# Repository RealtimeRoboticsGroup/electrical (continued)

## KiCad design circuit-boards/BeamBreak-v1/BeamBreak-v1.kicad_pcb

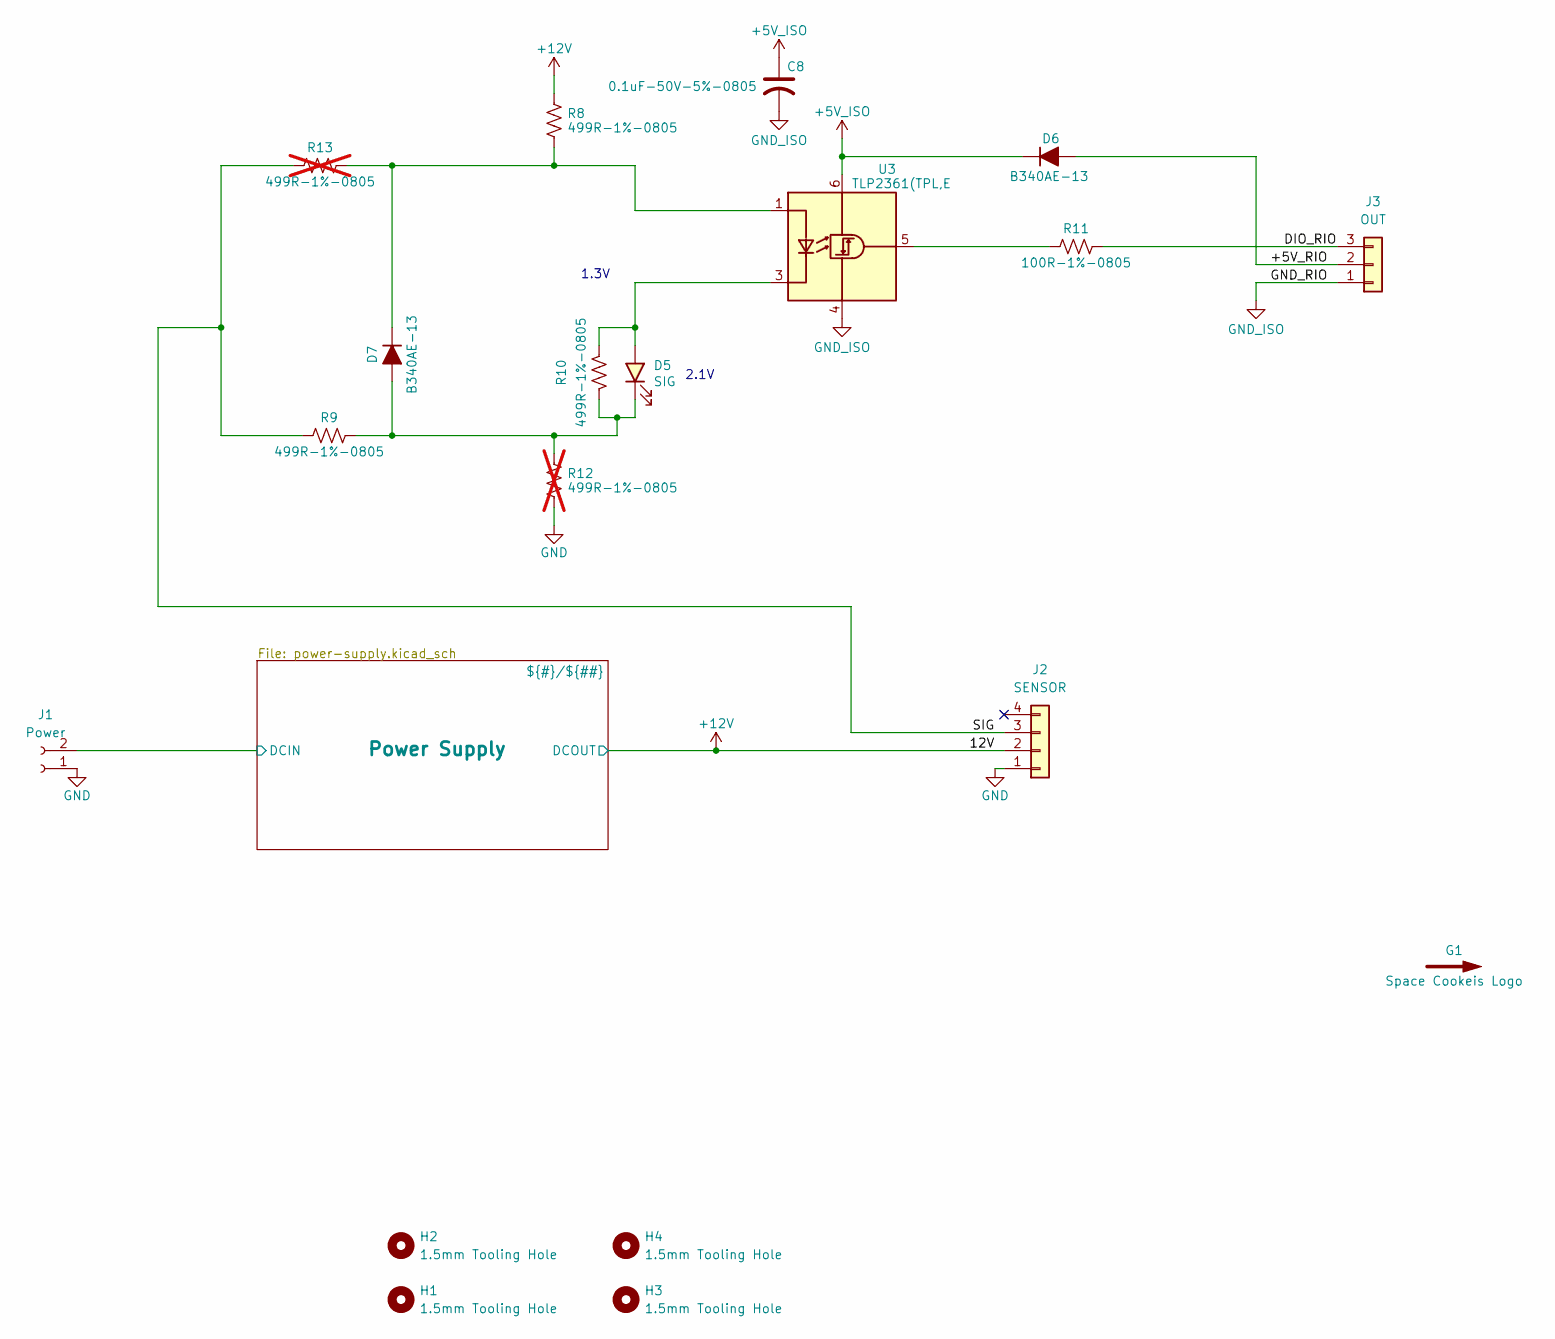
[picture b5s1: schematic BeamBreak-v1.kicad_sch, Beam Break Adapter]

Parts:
C8: 0.1uF-50V-5%-0805; C_0805_2012Metric_Pad1.18x1.45mm_HandSolder; MFG P/N C0805C104J5RACTU
D5: SIG; LED_1206_3216Metric; MFG P/N QTLP650D3TR
D6, D7: B340AE-13; D_SMA; MFG P/N B340AE-13
G1: Space Cookeis Logo; SPACE_COOKIES_LOGO_7mm
H1, H2, H3, H4: 1.5mm Tooling Hole; ToolingHole_1.5mm
J1: Power; Weidmuller-1824740000; MFG P/N 1824740000
J2: SENSOR; Molex-70555-0003; MFG P/N 70555-0038
J3: OUT; Molex-70555-0002; MFG P/N 70555-0037
R8, R9, R10: 499R-1%-0805; R_0805_2012Metric_Pad1.20x1.40mm_HandSolder; MFG P/N RC0805FR-07499RL
R11: 100R-1%-0805; R_0805_2012Metric_Pad1.20x1.40mm_HandSolder; MFG P/N CRG0805F100R
R12, R13: 499R-1%-0805; R_0805_2012Metric_Pad1.20x1.40mm_HandSolder; MFG P/N RC0805FR-07499RL; not fitted
U3: TLP2361(TPL,E; SO-5-6_4.55x3.7mm_P1.27mm; MFG P/N TLP2361(TPL,E

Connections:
+5V_ISO: C8.1, D6.1 (K), U3.6 (VDD)
+12V: J2.2, R8.2; also elsewhere on the board
/+5V_RIO: D6.2 (A), J3.2
/DIO_RIO: J3.3, R11.2
/Power Supply/DCIN: J1.2; also elsewhere on the board
/SIG: J2.3, R9.1, R13.1
GND: J1.1, J2.1, R12.1; also elsewhere on the board
GND_ISO: C8.2, J3.1, U3.4 (GND)
unnamed: D5.2 (A), R10.2, U3.3 (K)
unnamed: D5.1 (K), D7.2 (A), R9.2, R10.1, R12.2
unnamed: D7.1 (K), R8.1, R13.2, U3.1 (A)
unnamed: R11.1, U3.5 (VO)

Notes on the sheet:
2.1V
1.3V

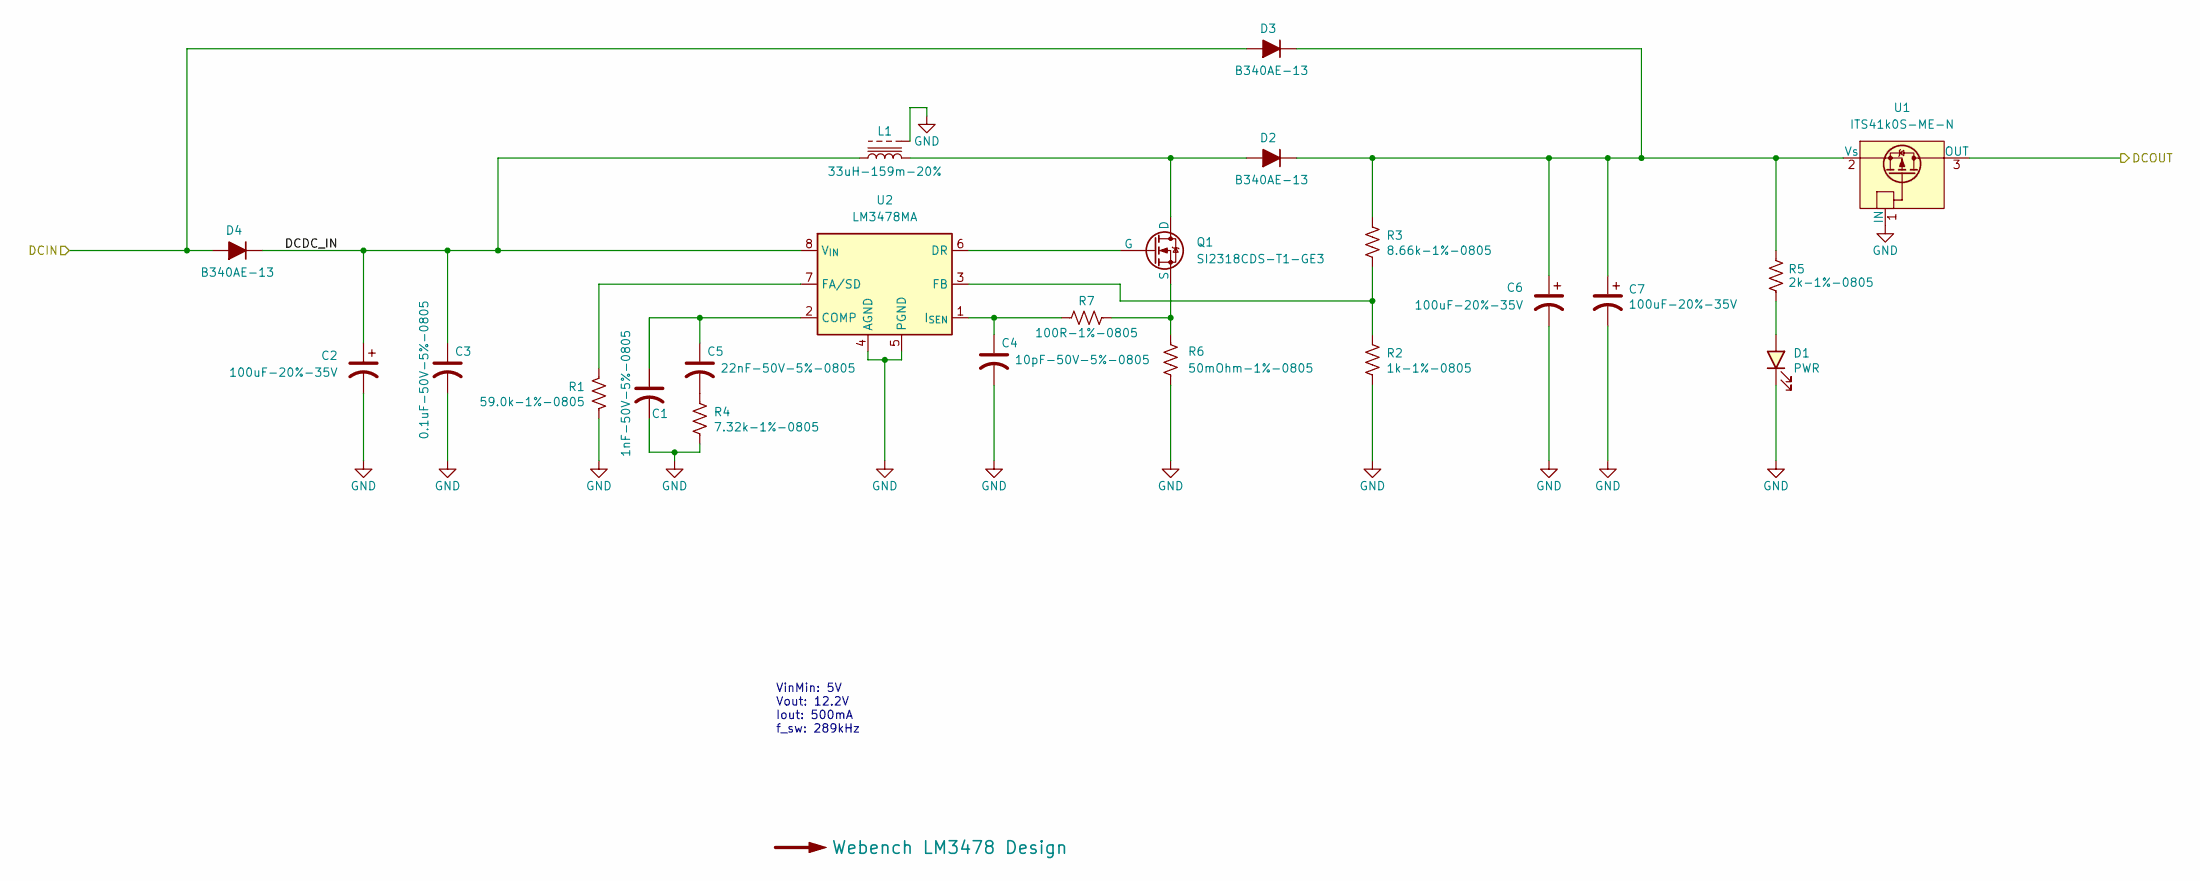
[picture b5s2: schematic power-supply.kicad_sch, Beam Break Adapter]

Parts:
C1: 1nF-50V-5%-0805; C_0805_2012Metric_Pad1.18x1.45mm_HandSolder; MFG P/N C0805C102J5GACTU
C2, C6, C7: 100uF-20%-35V; CP_Radial_D6.3mm_P2.50mm; MFG P/N RPF0608101M035K
C3: 0.1uF-50V-5%-0805; C_0805_2012Metric_Pad1.18x1.45mm_HandSolder; MFG P/N C0805C104J5RACTU
C4: 10pF-50V-5%-0805; C_0805_2012Metric_Pad1.18x1.45mm_HandSolder; MFG P/N CC0805JRNPO9BN100
C5: 22nF-50V-5%-0805; C_0805_2012Metric_Pad1.18x1.45mm_HandSolder; MFG P/N C2012C0G1H223J125AA
D1: PWR; LED_1206_3216Metric; MFG P/N QTLP650D4TR/QT15-21SYGD/S530-E2/TR8
D2, D3, D4: B340AE-13; D_SMA; MFG P/N B340AE-13
L1: 33uH-159m-20%; VishayDale-IHLE3232; MFG P/N IHLE3232DDER330M5A
Q1: SI2318CDS-T1-GE3; SOT-23-3; MFG P/N SI2318CDS-T1-GE3
R1: 59.0k-1%-0805; R_0805_2012Metric_Pad1.20x1.40mm_HandSolder; MFG P/N RC0805FR-0759KL
R2: 1k-1%-0805; R_0805_2012Metric_Pad1.20x1.40mm_HandSolder; MFG P/N RC0805FR-071KL
R3: 8.66k-1%-0805; R_0805_2012Metric_Pad1.20x1.40mm_HandSolder; MFG P/N RMCF0805FT8K66
R4: 7.32k-1%-0805; R_0805_2012Metric_Pad1.20x1.40mm_HandSolder; MFG P/N ERJ-6ENF7321V
R5: 2k-1%-0805; R_0805_2012Metric_Pad1.20x1.40mm_HandSolder; MFG P/N CRCW08052K00FKEA
R6: 50mOhm-1%-0805; R_0805_2012Metric_Pad1.20x1.40mm_HandSolder; MFG P/N ERJ-6BWFR050V
R7: 100R-1%-0805; R_0805_2012Metric_Pad1.20x1.40mm_HandSolder; MFG P/N CRG0805F100R
U1: ITS41k0S-ME-N; SOT-223-3_TabPin2; MFG P/N ITS41K0SMENHUMA1
U2: LM3478MA; SOIC-8_3.9x4.9mm_P1.27mm; MFG P/N LM3478MAX/NOPB

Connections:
+12V: U1.3 (OUT); also elsewhere on the board
/Power Supply/DCDC_IN: C2.1, C3.1, D4.1 (K), L1.1, U2.8 (V_{IN})
/Power Supply/DCIN: D3.2 (A), D4.2 (A); also elsewhere on the board
GND: C1.2, C2.2, C3.2, C4.2, C6.2, C7.2, D1.1 (K), L1.3, R1.1, R2.1, R4.1, R6.2, U1.1 (IN), U2.4 (AGND), U2.5 (PGND); also elsewhere on the board
unnamed: C5.2, R4.2
unnamed: D1.2 (A), R5.1
unnamed: D2.2 (A), L1.2, Q1.3 (D)
unnamed: C6.1, C7.1, D2.1 (K), D3.1 (K), R3.2, R5.2, U1.2 (Vs)
unnamed: Q1.1 (G), U2.6 (DR)
unnamed: Q1.2 (S), R6.1, R7.2
unnamed: C1.1, C5.1, U2.2 (COMP)
unnamed: R1.2, U2.7 (FA/SD)
unnamed: R2.2, R3.1, U2.3 (FB)
unnamed: C4.1, R7.1, U2.1 (I_{SEN})

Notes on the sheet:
VinMin: 5V Vout: 12.2V Iout: 500mA f_sw: 289kHz

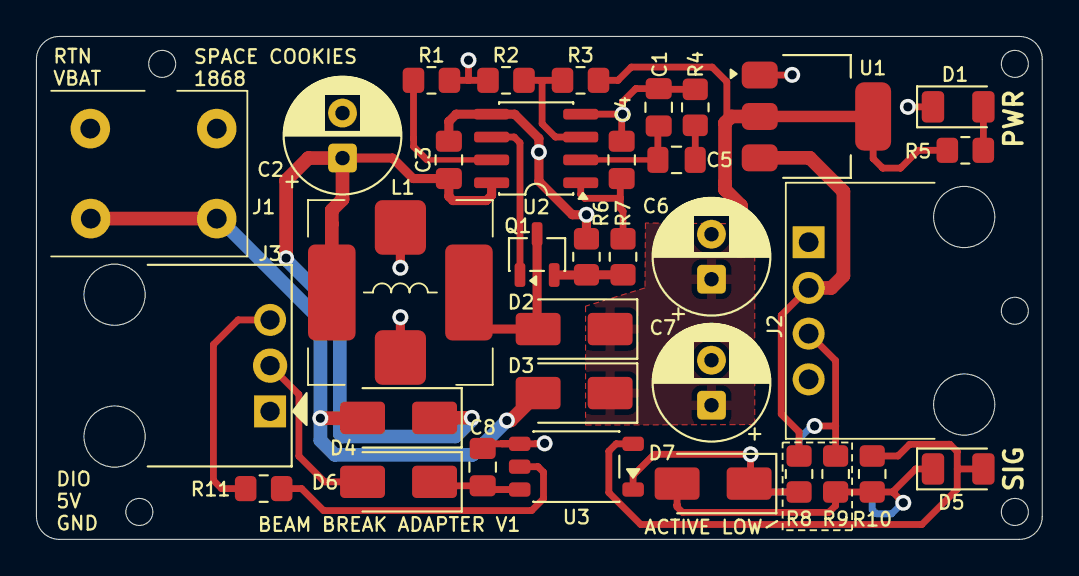
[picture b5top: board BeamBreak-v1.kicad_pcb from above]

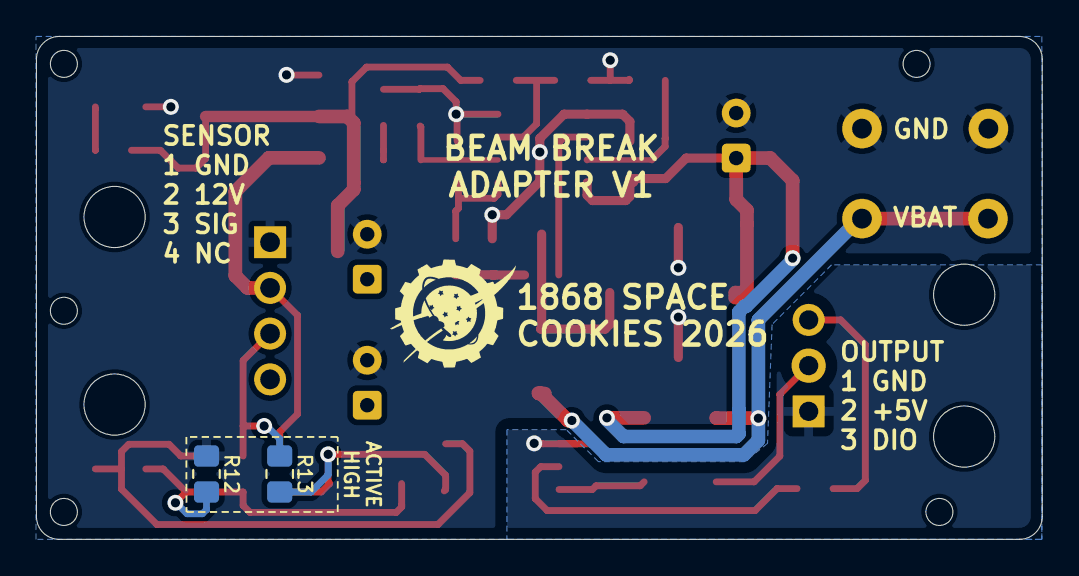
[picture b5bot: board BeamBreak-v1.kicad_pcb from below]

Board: 2 copper layers, 55.9 x 27.9 mm, 41 parts (3 on the bottom side), 23 nets.

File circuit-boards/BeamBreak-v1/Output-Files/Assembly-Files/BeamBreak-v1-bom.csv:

"Item","QUANTITY","Reference","Value","MFG","MFG P/N","DIST","DIST P/N"
"1","1","C1","1nF-50V-5%-0805","KEMET","C0805C102J5GACTU","Digikey","399-C0805C102J5GACTUCT-ND"
"2","1","C4","10pF-50V-5%-0805","YAGEO","CC0805JRNPO9BN100","Digikey","311-1099-1-ND"
"3","1","C5","22nF-50V-5%-0805","TDK Corporation","C2012C0G1H223J125AA","Digikey","445-7522-1-ND"
"4","3","C2,C6,C7","100uF-20%-35V","KYOCERA AVX","RPF0608101M035K","Digikey","478-RPF0608101M035KCT-ND"
"5","2","C3,C8","0.1uF-50V-5%-0805","KEMET","C0805C104J5RACTU","Digikey","399-C0805C104J5RACTUCT-ND"
"6","1","D1","PWR","Everlight","QTLP650D4TR/QT15-21SYGD/S530-E2/TR8","Digikey","1080-1419-1-ND"
"7","1","D5","SIG","Everlight","QTLP650D3TR","Digikey","1080-1418-1-ND"
"8","5","D2-D4,D6,D7","B340AE-13","Diodes Inc","B340AE-13","Digikey","B340AE-13DICT-ND"
"9","1","J1","Power","Weidmuller","1824740000","Digikey","281-2110-ND"
"10","1","J2","SENSOR","Molex","70555-0038","Digikey","WM4177-ND"
"11","1","J3","OUT","Molex","70555-0037","Digikey","WM4176-ND"
"12","1","L1","33uH-159m-20%","Vishay Dale","IHLE5050FHER6R8M5A","Digikey","541-IHLE5050FHER6R8M5ACT-ND"
"13","1","Q1","SI2318CDS-T1-GE3","Vishay Siliconix","SI2318CDS-T1-GE3","Digikey","SI2318CDS-T1-GE3CT-ND"
"14","1","R1","59.0k-1%-0805","YAGEO","RC0805FR-0759KL","Digikey","311-59.0KCRCT-ND"
"15","1","R2","1k-1%-0805","YAGEO","RC0805FR-071KL","Digikey","311-1.00KCRCT-ND"
"16","1","R3","8.66k-1%-0805","Stackpole Electronics Inc","RMCF0805FT8K66","Digikey","RMCF0805FT8K66CT-ND"
"17","1","R4","7.32k-1%-0805","Panasonic Electronic Components","ERJ-6ENF7321V","Digikey","P7.32KCCT-ND"
"18","1","R5","2k-1%-0805","Vishay Dale","CRCW08052K00FKEA","Digikey","541-2.00KCCT-ND"
"19","1","R6","50mOhm-1%-0805","Panasonic Electronic Components","ERJ-6BWFR050V","Digikey","P17581CT-ND"
"20","2","R7,R11","100R-1%-0805","TE Connectivity Passive Product","CRG0805F100R","Digikey","A106053CT-ND"
"21","3","R8-R10","499R-1%-0805","YAGEO","RC0805FR-07499RL","Digikey","311-499CRCT-ND"
"22","1","U1","ITS41k0S-ME-N","Infineon","ITS41K0SMENHUMA1","Digikey","ITS41K0SMENHUMA1CT-ND"
"23","1","U2","LM3478MA","Texas Instruments","LM3478MAX/NOPB","Digikey","296-38111-1-ND"
"24","1","U3","TLP2361(TPL,E","Toshiba Semiconductor and Storage","TLP2361(TPL,E","Digikey","TLP2361(TPLECT-ND"

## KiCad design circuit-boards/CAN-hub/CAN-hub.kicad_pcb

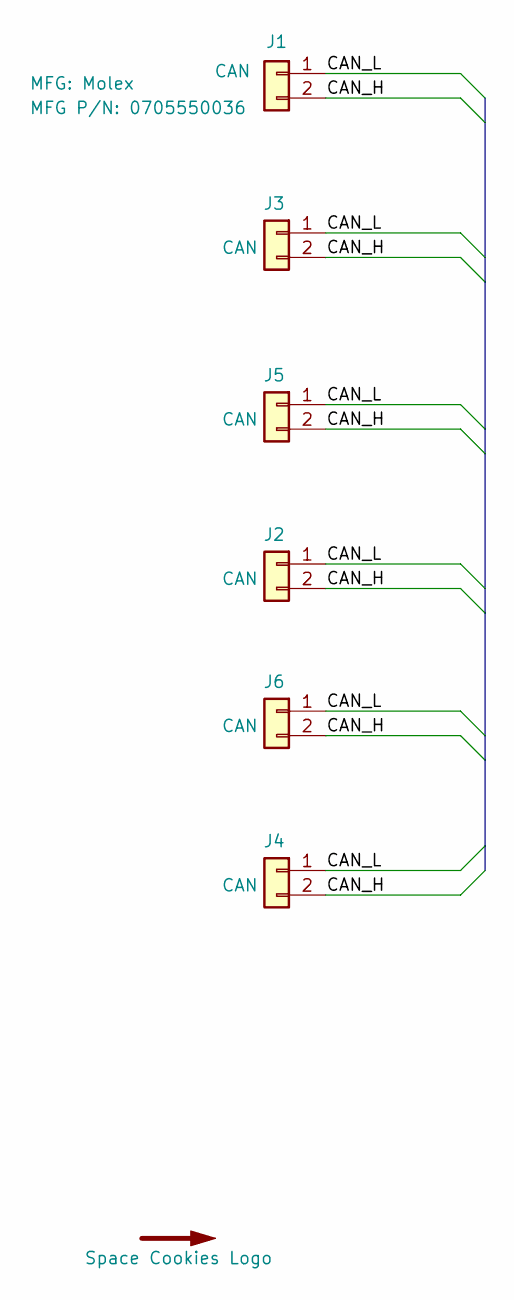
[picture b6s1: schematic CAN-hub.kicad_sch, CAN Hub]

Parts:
G1: Space Cookies Logo; SPACE_COOKIES_LOGO_7mm
J1, J2, J3, J4, J5, J6: CAN; Molex-70555-0001; MFG P/N 0705550036

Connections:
/CAN_H: J1.2, J2.2, J3.2, J4.2, J5.2, J6.2
/CAN_L: J1.1, J2.1, J3.1, J4.1, J5.1, J6.1

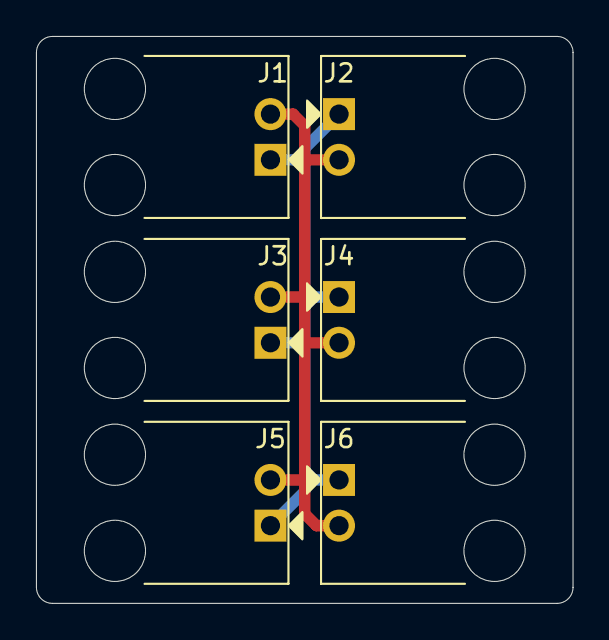
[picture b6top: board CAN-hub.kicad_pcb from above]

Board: 2 copper layers, 29.8 x 31.5 mm, 7 parts (1 on the bottom side), 2 nets.

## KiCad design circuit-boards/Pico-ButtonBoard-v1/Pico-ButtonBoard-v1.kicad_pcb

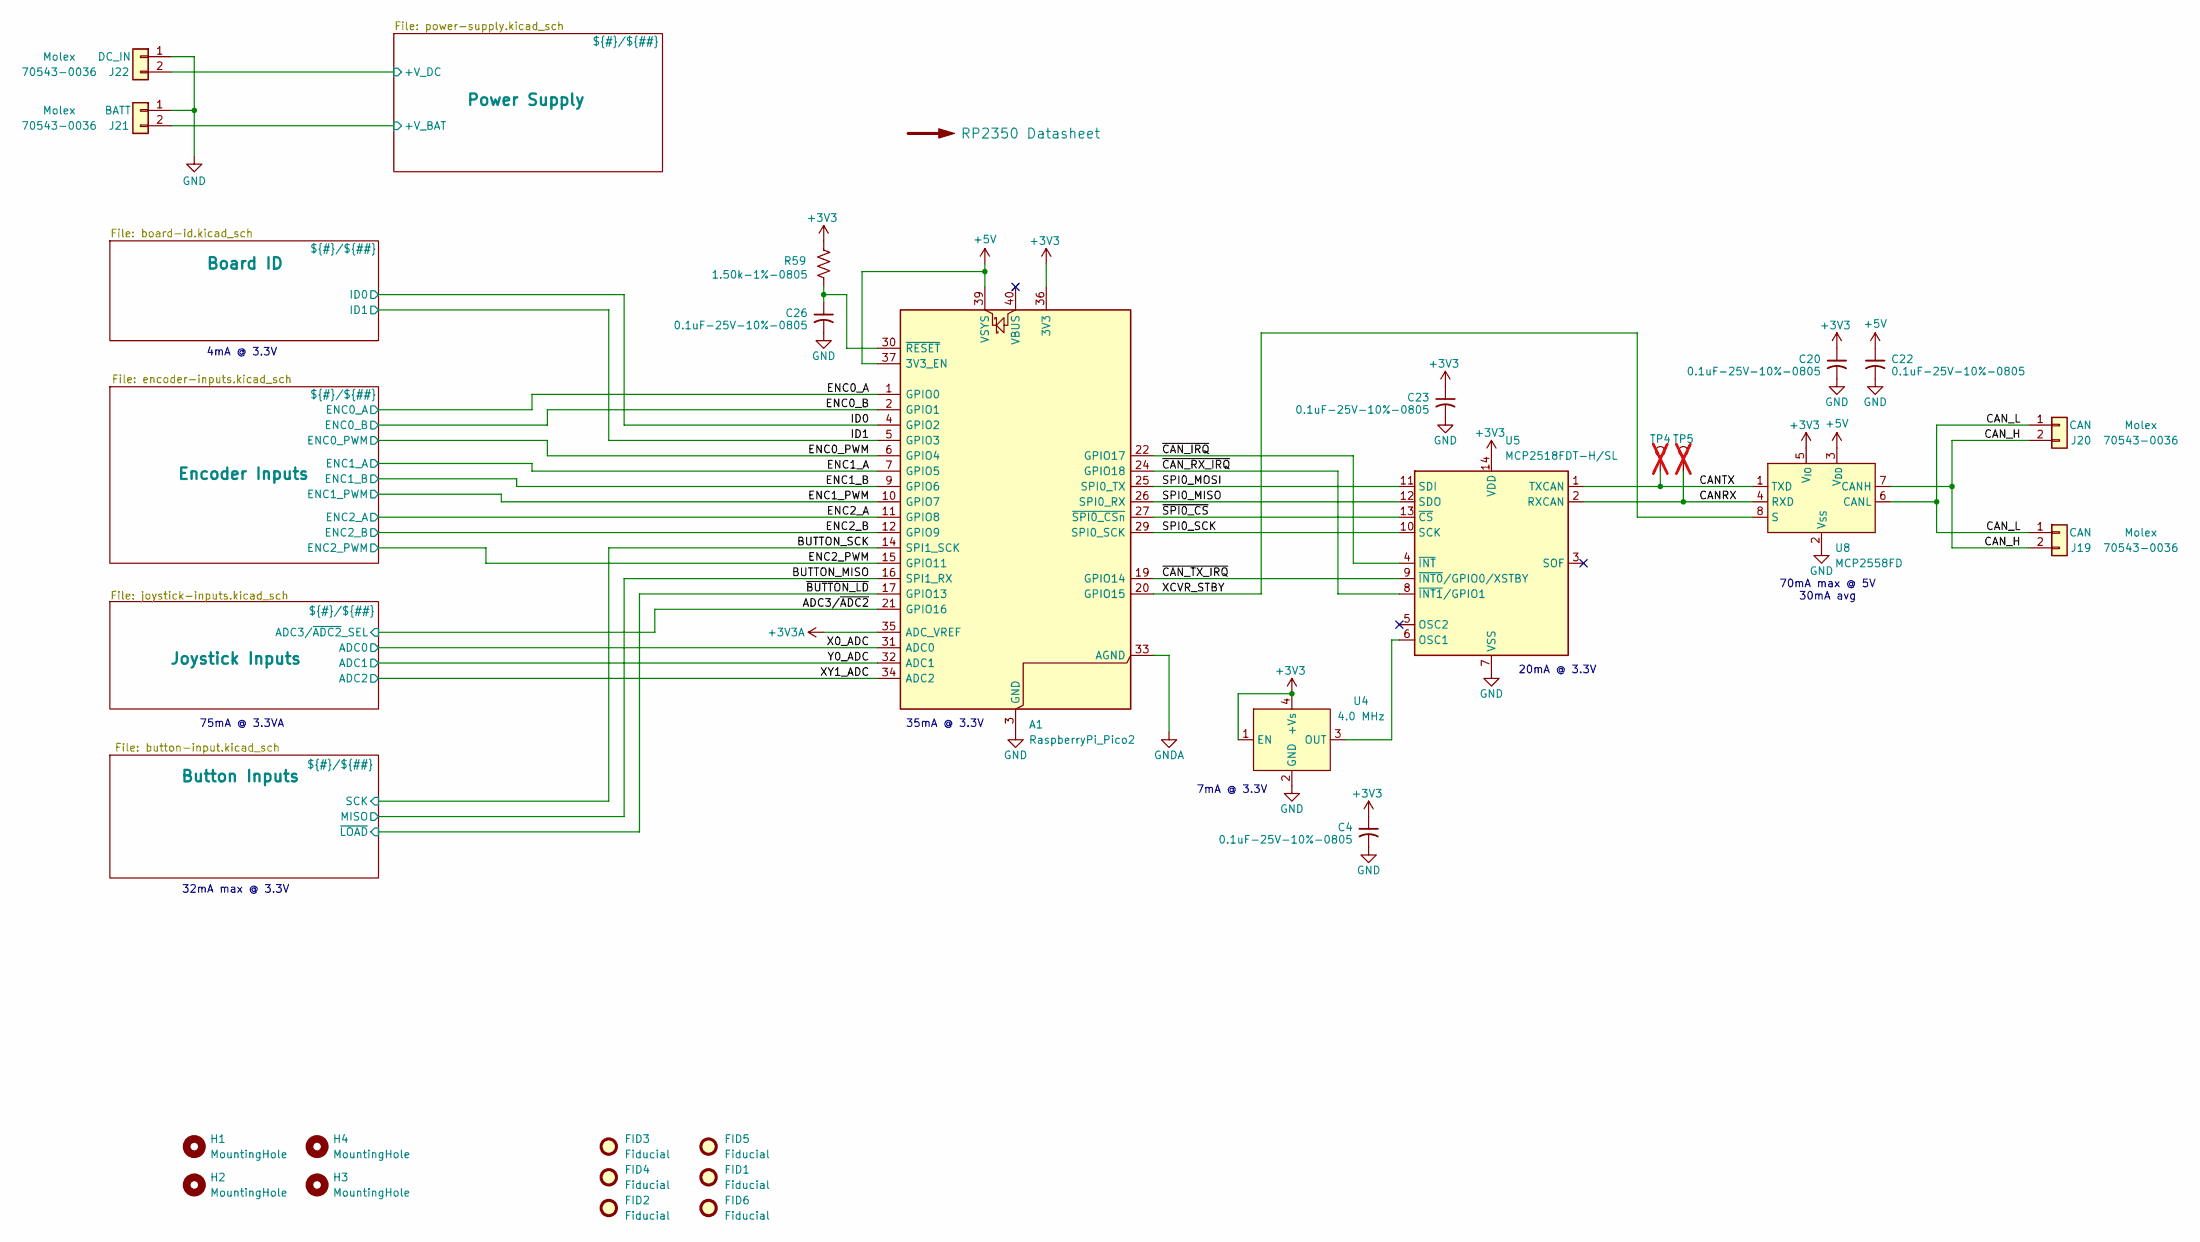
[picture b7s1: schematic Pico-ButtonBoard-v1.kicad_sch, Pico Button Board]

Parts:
A1: RaspberryPi_Pico2; RaspberryPi_Pico_Common_Unspecified
C4, C20, C22, C23, C26: 0.1uF-25V-10%-0805; C_0805_2012Metric_Pad1.18x1.45mm_HandSolder; MFG P/N 311-1141-1-ND
FID1, FID2, FID3, FID4, FID5, FID6: Fiducial; Fiducial_1.6mm_Mask3mm
H1, H2, H3, H4: MountingHole; MountingHole_3.2mm_M3
J19, J20: CAN; Molex-70543-0001; MFG P/N 70543-0036
J21: BATT; Molex-70543-0001; MFG P/N 70543-0036
J22: DC_IN; Molex-70543-0001; MFG P/N 70543-0036
R59: 1.50k-1%-0805; R_0805_2012Metric_Pad1.20x1.40mm_HandSolder; MFG P/N RC0805FR-071K5L
TP4: CAN_TX; TestPoint_Keystone_5000-5004_Miniature; not fitted
TP5: CAN_RX; TestPoint_Keystone_5000-5004_Miniature; not fitted
U4: 4.0 MHz; Wurth-CFPS-73; MFG P/N 831018041
U5: MCP2518FDT-H/SL; SO-14_3.9x8.65mm_P1.27mm; MFG P/N MCP2518FDT-H/SL
U8: MCP2558FD; SO-8_3.9x4.9mm_P1.27mm; MFG P/N MCP2558FD-H/SN

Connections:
+3V3: A1.36 (3V3), C4.1, C20.1, C23.1, R59.1, U4.1 (EN), U4.4 (+Vs), U5.14 (VDD), U8.5 (V_{IO}); also elsewhere on the board
+3V3A: A1.35 (ADC_VREF); also elsewhere on the board
+5V: A1.37 (3V3_EN), A1.39 (VSYS), C22.1, U8.3 (V_{DD}); also elsewhere on the board
/ADC3/~ADC2: A1.21 (GPIO16); also elsewhere on the board
/BUTTON_MISO: A1.16 (SPI1_RX); also elsewhere on the board
/BUTTON_SCK: A1.14 (SPI1_SCK); also elsewhere on the board
/CANRX: TP5.1, U5.2 (RXCAN), U8.4 (RXD)
/CANTX: TP4.1, U5.1 (TXCAN), U8.1 (TXD)
/CAN_H: J19.2, J20.2, U8.7 (CANH)
/CAN_L: J19.1, J20.1, U8.6 (CANL)
/ENC0_A: A1.1 (GPIO0); also elsewhere on the board
/ENC0_B: A1.2 (GPIO1); also elsewhere on the board
/ENC0_PWM: A1.6 (GPIO4); also elsewhere on the board
/ENC1_A: A1.7 (GPIO5); also elsewhere on the board
/ENC1_B: A1.9 (GPIO6); also elsewhere on the board
/ENC1_PWM: A1.10 (GPIO7); also elsewhere on the board
/ENC2_A: A1.11 (GPIO8); also elsewhere on the board
/ENC2_B: A1.12 (GPIO9); also elsewhere on the board
/ENC2_PWM: A1.15 (GPIO11); also elsewhere on the board
/ID0: A1.4 (GPIO2); also elsewhere on the board
/ID1: A1.5 (GPIO3); also elsewhere on the board
/Power Supply/+V_BAT: J21.2; also elsewhere on the board
/Power Supply/+V_DC: J22.2; also elsewhere on the board
/SPI0_MISO: A1.26 (SPI0_RX), U5.12 (SDO)
/SPI0_MOSI: A1.25 (SPI0_TX), U5.11 (SDI)
/SPI0_SCK: A1.29 (SPI0_SCK), U5.10 (SCK)
/X0_ADC: A1.31 (ADC0); also elsewhere on the board
/XCVR_STBY: A1.20 (GPIO15), U8.8 (S)
/XY1_ADC: A1.34 (ADC2); also elsewhere on the board
/Y0_ADC: A1.32 (ADC1); also elsewhere on the board
/~BUTTON_LD: A1.17 (GPIO13); also elsewhere on the board
/~CAN_IRQ: A1.22 (GPIO17), U5.4 (~INT)
/~CAN_RX_IRQ: A1.24 (GPIO18), U5.8 (~INT1/GPIO1)
/~CAN_TX_IRQ: A1.19 (GPIO14), U5.9 (~INT0/GPIO0/XSTBY)
/~SPI0_CS: A1.27 (~SPI0_CSn), U5.13 (~CS)
GND: A1.3 (GND), A1.8 (GND), A1.13 (GND), A1.18 (GND), A1.23 (GND), A1.28 (GND), A1.38 (GND), C4.2, C20.2, C22.2, C23.2, C26.2, J21.1, J22.1, U4.2 (GND), U5.7 (VSS), U8.2 (V_{SS}); also elsewhere on the board
GNDA: A1.33 (AGND); also elsewhere on the board
unnamed: A1.30 (~RESET), C26.1, R59.2
unnamed: U4.3 (OUT), U5.6 (OSC1)

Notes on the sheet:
32mA max @ 3.3V
20mA @ 3.3V
35mA @ 3.3V
75mA @ 3.3VA
4mA @ 3.3V
7mA @ 3.3V
70mA max @ 5V 30mA avg

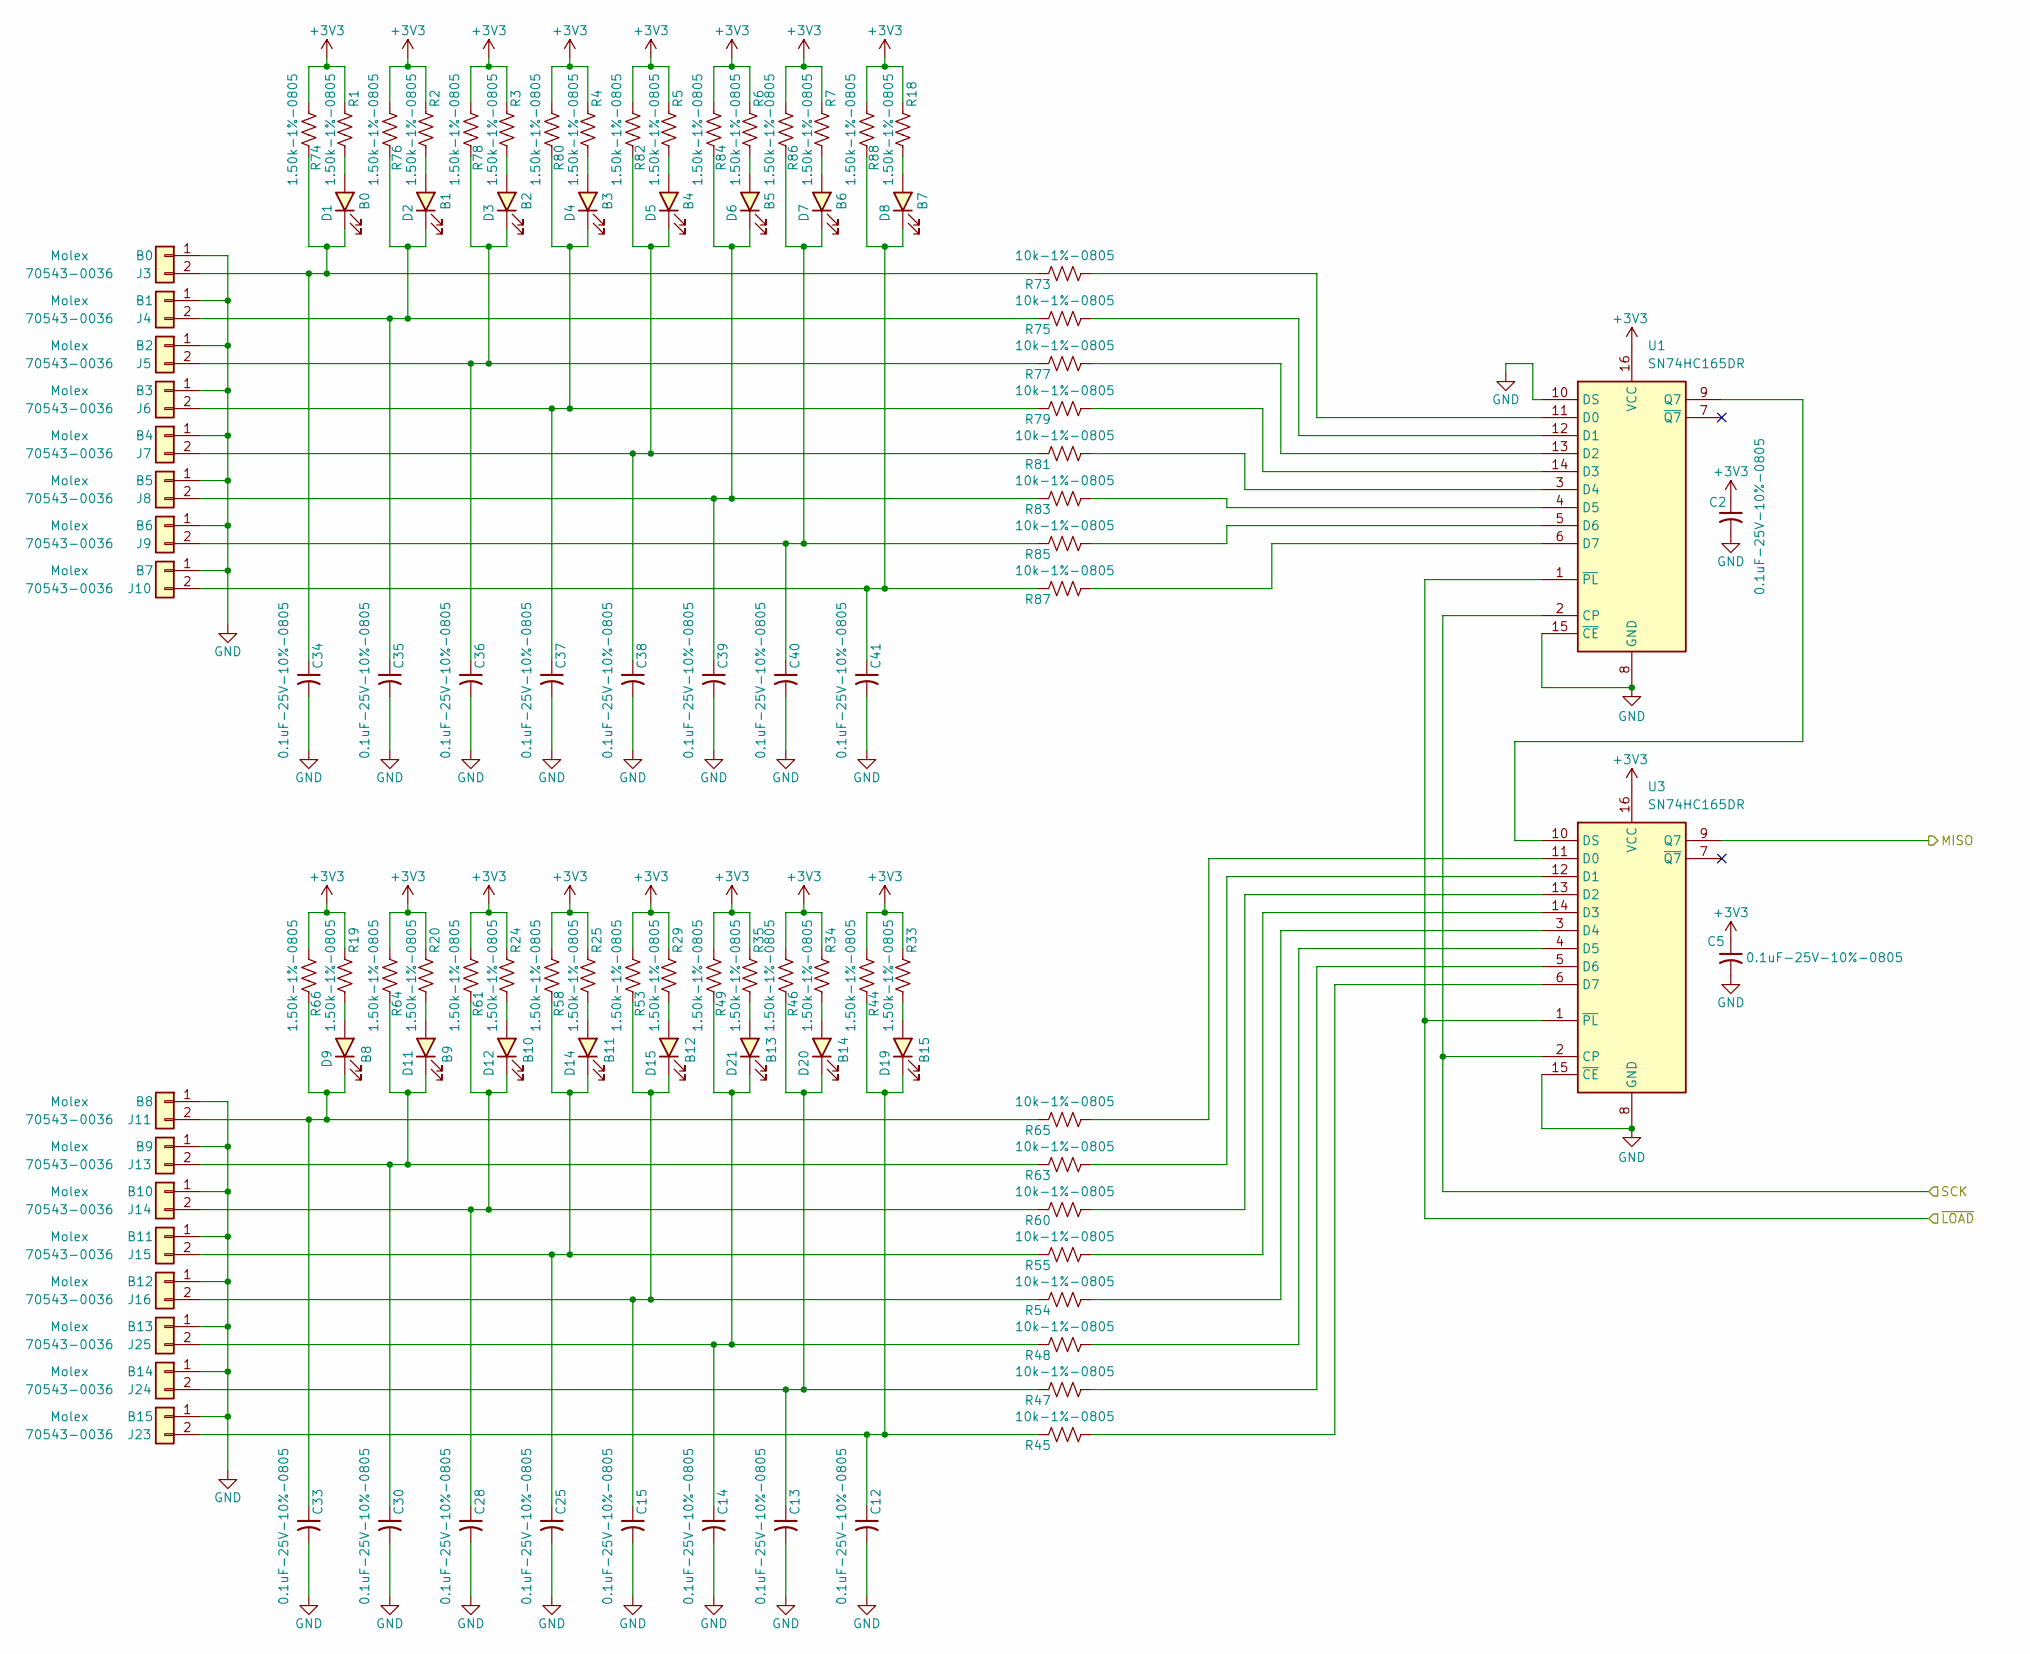
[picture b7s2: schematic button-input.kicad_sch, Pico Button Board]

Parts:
C2, C5, C12, C13, C14, C15, C25, C28, C30, C33, C34, C35, C36, C37, C38, C39, C40, C41: 0.1uF-25V-10%-0805; C_0805_2012Metric_Pad1.18x1.45mm_HandSolder; MFG P/N 311-1141-1-ND
D1: B0; LED_1206_3216Metric; MFG P/N QTLP650D4TR/QT15-21SYGD/S530-E2/TR8
D2: B1; LED_1206_3216Metric; MFG P/N QTLP650D4TR/QT15-21SYGD/S530-E2/TR8
D3: B2; LED_1206_3216Metric; MFG P/N QTLP650D4TR/QT15-21SYGD/S530-E2/TR8
D4: B3; LED_1206_3216Metric; MFG P/N QTLP650D4TR/QT15-21SYGD/S530-E2/TR8
D5: B4; LED_1206_3216Metric; MFG P/N QTLP650D4TR/QT15-21SYGD/S530-E2/TR8
D6: B5; LED_1206_3216Metric; MFG P/N QTLP650D4TR/QT15-21SYGD/S530-E2/TR8
D7: B6; LED_1206_3216Metric; MFG P/N QTLP650D4TR/QT15-21SYGD/S530-E2/TR8
D8: B7; LED_1206_3216Metric; MFG P/N QTLP650D4TR/QT15-21SYGD/S530-E2/TR8
D9: B8; LED_1206_3216Metric; MFG P/N QTLP650D4TR/QT15-21SYGD/S530-E2/TR8
D11: B9; LED_1206_3216Metric; MFG P/N QTLP650D4TR/QT15-21SYGD/S530-E2/TR8
D12: B10; LED_1206_3216Metric; MFG P/N QTLP650D4TR/QT15-21SYGD/S530-E2/TR8
D14: B11; LED_1206_3216Metric; MFG P/N QTLP650D4TR/QT15-21SYGD/S530-E2/TR8
D15: B12; LED_1206_3216Metric; MFG P/N QTLP650D4TR/QT15-21SYGD/S530-E2/TR8
D19: B15; LED_1206_3216Metric; MFG P/N QTLP650D4TR/QT15-21SYGD/S530-E2/TR8
D20: B14; LED_1206_3216Metric; MFG P/N QTLP650D4TR/QT15-21SYGD/S530-E2/TR8
D21: B13; LED_1206_3216Metric; MFG P/N QTLP650D4TR/QT15-21SYGD/S530-E2/TR8
J3: B0; Molex-70543-0001; MFG P/N 70543-0036
J4: B1; Molex-70543-0001; MFG P/N 70543-0036
J5: B2; Molex-70543-0001; MFG P/N 70543-0036
J6: B3; Molex-70543-0001; MFG P/N 70543-0036
J7: B4; Molex-70543-0001; MFG P/N 70543-0036
J8: B5; Molex-70543-0001; MFG P/N 70543-0036
J9: B6; Molex-70543-0001; MFG P/N 70543-0036
J10: B7; Molex-70543-0001; MFG P/N 70543-0036
J11: B8; Molex-70543-0001; MFG P/N 70543-0036
J13: B9; Molex-70543-0001; MFG P/N 70543-0036
J14: B10; Molex-70543-0001; MFG P/N 70543-0036
J15: B11; Molex-70543-0001; MFG P/N 70543-0036
J16: B12; Molex-70543-0001; MFG P/N 70543-0036
J23: B15; Molex-70543-0001; MFG P/N 70543-0036
J24: B14; Molex-70543-0001; MFG P/N 70543-0036
J25: B13; Molex-70543-0001; MFG P/N 70543-0036
R1, R2, R3, R4, R5, R6, R7, R18, R19, R20, R24, R25, R29, R33, R34, R35, R44, R46, R49, R53, R58, R61, R64, R66, R74, R76, R78, R80, R82, R84, R86, R88: 1.50k-1%-0805; R_0805_2012Metric_Pad1.20x1.40mm_HandSolder; MFG P/N RC0805FR-071K5L
R45, R47, R48, R54, R55, R60, R63, R65, R73, R75, R77, R79, R81, R83, R85, R87: 10k-1%-0805; R_0805_2012Metric_Pad1.20x1.40mm_HandSolder; MFG P/N CRCW080510K0FKEA
U1, U3: SN74HC165DR; SO-16_3.9x9.9mm_P1.27mm; MFG P/N SN74HC165DR

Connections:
+3V3: C2.1, C5.1, R1.1, R2.1, R3.1, R4.1, R5.1, R6.1, R7.1, R18.1, R19.1, R20.1, R24.1, R25.1, R29.1, R33.1, R34.1, R35.1, R44.1, R46.1, R49.1, R53.1, R58.1, R61.1, R64.1, R66.1, R74.1, R76.1, R78.1, R80.1, R82.1, R84.1, R86.1, R88.1, U1.16 (VCC), U3.16 (VCC); also elsewhere on the board
/BUTTON_MISO: U3.9 (Q7); also elsewhere on the board
/BUTTON_SCK: U1.2 (CP), U3.2 (CP); also elsewhere on the board
/~BUTTON_LD: U1.1 (~PL), U3.1 (~PL); also elsewhere on the board
GND: C2.2, C5.2, C12.2, C13.2, C14.2, C15.2, C25.2, C28.2, C30.2, C33.2, C34.2, C35.2, C36.2, C37.2, C38.2, C39.2, C40.2, C41.2, J3.1, J4.1, J5.1, J6.1, J7.1, J8.1, J9.1, J10.1, J11.1, J13.1, J14.1, J15.1, J16.1, J23.1, J24.1, J25.1, U1.8 (GND), U1.10 (DS), U1.15 (~CE), U3.8 (GND), U3.15 (~CE); also elsewhere on the board
unnamed: D1.2 (A), R1.2
unnamed: C34.1, D1.1 (K), J3.2, R73.1, R74.2
unnamed: D2.2 (A), R2.2
unnamed: C35.1, D2.1 (K), J4.2, R75.1, R76.2
unnamed: D3.2 (A), R3.2
unnamed: C36.1, D3.1 (K), J5.2, R77.1, R78.2
unnamed: D4.2 (A), R4.2
unnamed: C37.1, D4.1 (K), J6.2, R79.1, R80.2
unnamed: D5.2 (A), R5.2
unnamed: C38.1, D5.1 (K), J7.2, R81.1, R82.2
unnamed: D6.2 (A), R6.2
unnamed: C39.1, D6.1 (K), J8.2, R83.1, R84.2
unnamed: D7.2 (A), R7.2
unnamed: C40.1, D7.1 (K), J9.2, R85.1, R86.2
unnamed: D8.2 (A), R18.2
unnamed: C41.1, D8.1 (K), J10.2, R87.1, R88.2
unnamed: D9.2 (A), R19.2
unnamed: C33.1, D9.1 (K), J11.2, R65.1, R66.2
unnamed: D11.2 (A), R20.2
unnamed: C30.1, D11.1 (K), J13.2, R63.1, R64.2
unnamed: D12.2 (A), R24.2
unnamed: C28.1, D12.1 (K), J14.2, R60.1, R61.2
unnamed: D14.2 (A), R25.2
unnamed: C25.1, D14.1 (K), J15.2, R55.1, R58.2
unnamed: D15.2 (A), R29.2
unnamed: C15.1, D15.1 (K), J16.2, R53.2, R54.1
unnamed: D19.2 (A), R33.2
unnamed: C12.1, D19.1 (K), J23.2, R44.2, R45.1
unnamed: D20.2 (A), R34.2
unnamed: C13.1, D20.1 (K), J24.2, R46.2, R47.1
unnamed: D21.2 (A), R35.2
unnamed: C14.1, D21.1 (K), J25.2, R48.1, R49.2
unnamed: R73.2, U1.11 (D0)
unnamed: R75.2, U1.12 (D1)
unnamed: R77.2, U1.13 (D2)
unnamed: R79.2, U1.14 (D3)
unnamed: R81.2, U1.3 (D4)
unnamed: R83.2, U1.4 (D5)
unnamed: R85.2, U1.5 (D6)
unnamed: R87.2, U1.6 (D7)
unnamed: U1.9 (Q7), U3.10 (DS)
unnamed: R65.2, U3.11 (D0)
unnamed: R63.2, U3.12 (D1)
unnamed: R60.2, U3.13 (D2)
unnamed: R55.2, U3.14 (D3)
unnamed: R54.2, U3.3 (D4)
unnamed: R48.2, U3.4 (D5)
unnamed: R47.2, U3.5 (D6)
unnamed: R45.2, U3.6 (D7)

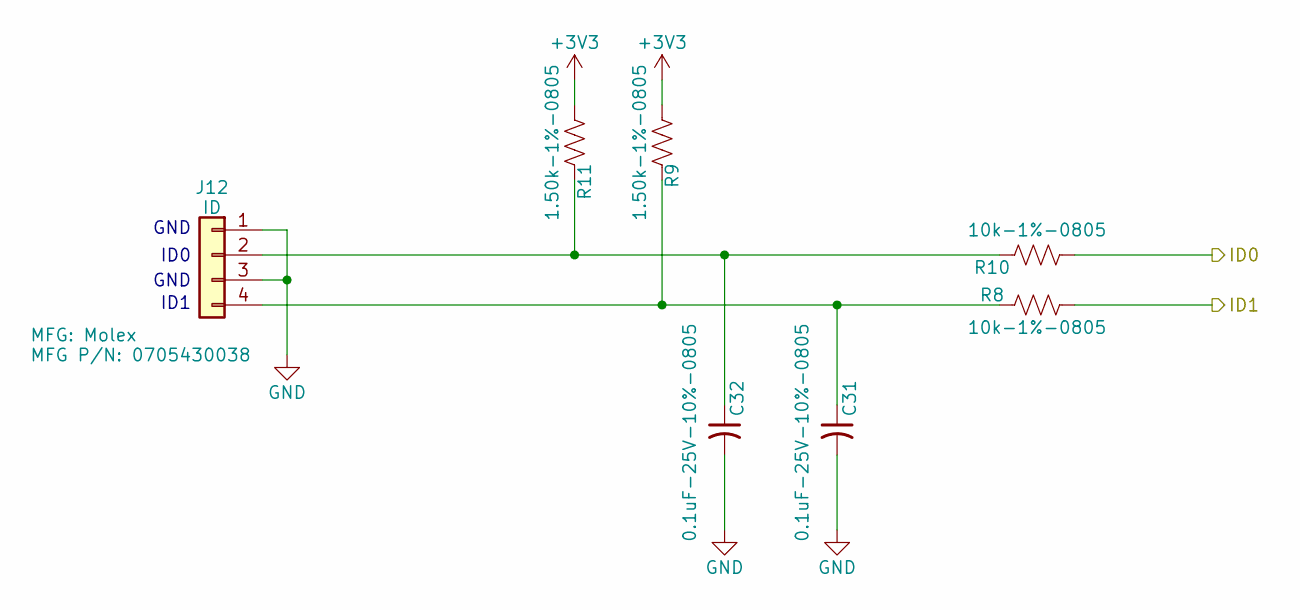
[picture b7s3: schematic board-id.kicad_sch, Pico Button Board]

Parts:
C31, C32: 0.1uF-25V-10%-0805; C_0805_2012Metric_Pad1.18x1.45mm_HandSolder; MFG P/N 311-1141-1-ND
J12: ID; Molex-70543-0003; MFG P/N 0705430038
R8, R10: 10k-1%-0805; R_0805_2012Metric_Pad1.20x1.40mm_HandSolder; MFG P/N CRCW080510K0FKEA
R9, R11: 1.50k-1%-0805; R_0805_2012Metric_Pad1.20x1.40mm_HandSolder; MFG P/N RC0805FR-071K5L

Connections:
+3V3: R9.1, R11.1; also elsewhere on the board
/ID0: R10.2; also elsewhere on the board
/ID1: R8.2; also elsewhere on the board
GND: C31.2, C32.2, J12.1, J12.3; also elsewhere on the board
unnamed: C32.1, J12.2, R10.1, R11.2
unnamed: C31.1, J12.4, R8.1, R9.2

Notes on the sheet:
GND
ID1
ID0
